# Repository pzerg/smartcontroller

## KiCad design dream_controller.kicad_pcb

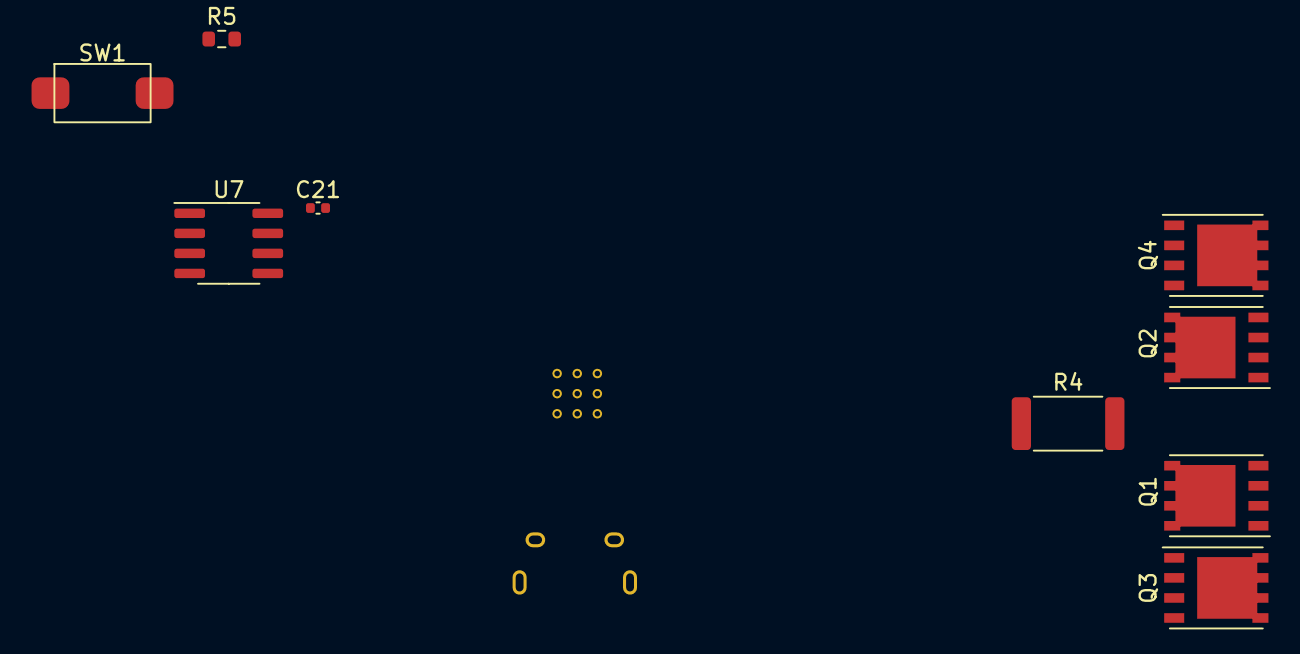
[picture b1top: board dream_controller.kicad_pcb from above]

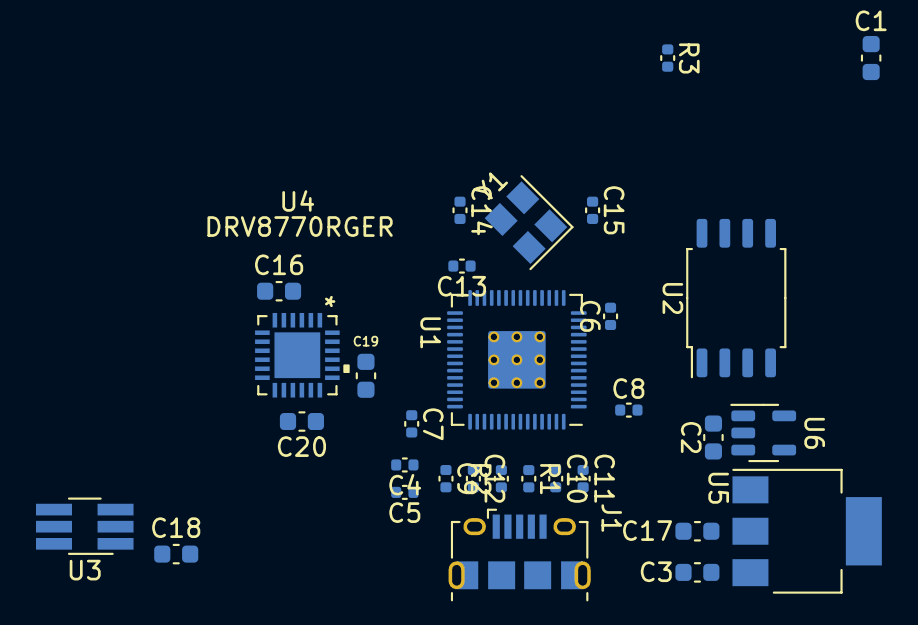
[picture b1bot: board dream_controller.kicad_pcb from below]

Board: 2 copper layers, 40 parts (31 on the bottom side), 30 nets, no tracks yet.

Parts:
C1: 100u; C_0603_1608Metric
C2, C3, C17: 10u; C_0603_1608Metric
C4, C5, C6, C7, C8, C9, C11, C12, C21: 100n; C_0402_1005Metric
C10, C13: 1u; C_0402_1005Metric
C14, C15: 14p; C_0402_1005Metric
C16: 10uF; C_0603_1608Metric
C18: 0.1u; C_0603_1608Metric
C19, C20: 100n; C_0603_1608Metric
J1: USB_B_Micro; USB_Micro-B_Amphenol_10118194_Horizontal
Q1, Q2, Q3, Q4: Q_NMOS_DGS; PowerPAK_SO-8_FET
R1, R2: 27; C_0402_1005Metric
R3: 1k; C_0402_1005Metric
R4: 0.3m; R_2512_6332Metric
R5: 1k; R_0603_1608Metric
SW1: SW_Push; PTS636
U1: RP2040; RP2040-QFN-56
U2: W25Q32JVSS; SOIC-8_5.23x5.23mm_P1.27mm
U3: MAX4073TAUT; TSOT-23-6_HandSoldering
U4: DRV8770RGER
U5: LM1117-3.3; SOT-223
U6: MAX40200AUK; SOT-23-5
U7: MAX3051; SOIC-8_3.9x4.9mm_P1.27mm
Y1: Crystal; Crystal_SMD_3225-4Pin_3.2x2.5mm

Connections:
+1V1: C11.1, C12.1, C13.1, U1.23 (DVDD), U1.45 (VREG_VOUT), U1.50 (DVDD)
+3V3: C1.1, C4.1, C5.1, C6.1, C7.1, C8.1, C9.1, C10.1, C17.1, C18.2, C21.2, R3.1, U1.1 (IOVDD), U1.10 (IOVDD), U1.22 (IOVDD), U1.33 (IOVDD), U1.42 (IOVDD), U1.43 (ADC_AVDD), U1.44 (VREG_IN), U1.48 (USB_VDD), U1.49 (IOVDD), U2.8 (VCC), U3.3 (VCC), U5.2 (VO), U7.3 (VDD)
+15V: C3.1, C16.2, U4.4 (GVDD), U5.3 (VI), U6.5 (OUT)
/CAN_RX: U1.18 (GPIO15), U7.4 (RXD)
/CAN_TX: U1.27 (GPIO16), U7.1 (TXD)
/Driver/GHA: Q1.2 (G), U4.19 (GHA)
/Driver/GHB: Q2.2 (G), U4.16 (GHB)
/Driver/GLA: Q3.2 (G), U4.11 (GLA)
/Driver/GLB: Q4.2 (G), U4.10 (GLB)
/Driver/M_A: Q1.3 (S), Q3.1 (D)
/Driver/M_B: Q2.3 (S), Q4.1 (D)
/Driver/RS-: Q1.1 (D), Q2.1 (D), R4.2, U3.5 (RS-)
/F_CLK: U1.52 (QSPI_SCLK), U2.6 (CLK)
/F_D0: U1.53 (QSPI_SD0), U2.5 (DI(IO0))
/F_D1: U1.55 (QSPI_SD1), U2.2 (DO(IO1))
/F_D2: U1.54 (QSPI_SD2), U2.3 (IO2)
/F_D3: U1.51 (QSPI_SD3), U2.7 (IO3)
/SS: R3.2, R5.2, U1.56 (QSPI_SS), U2.1 (~CS)
/USB_D+: J1.3 (D+), R1.2
/USB_D-: J1.2 (D-), R2.1
/VBUS: C2.1, J1.1 (VBUS), U6.1 (VDD), U6.3 (EN)
/XIN: C14.2, U1.20 (XIN), Y1.1
/XOUT: C15.2, U1.21 (XOUT), Y1.2
GND: C1.2, C2.2, C3.2, C4.2, C5.2, C6.2, C7.2, C8.2, C9.2, C10.2, C11.2, C12.2, C13.2, C14.1, C15.1, C16.1, C17.2, C18.1, C21.1, J1.5 (GND), J1.6 (Shield), Q3.3 (S), Q4.3 (S), SW1.1, U1.19 (TESTEN), U1.57 (GND), U2.4 (GND), U3.1 (GND), U3.2 (GND), U4.6 (GND), U4.12 (RSVD4), U4.25 (EPAD), U5.1 (GND), U6.2 (GND), U7.2 (GND), U7.5 (SHDN), U7.8 (RS)
unnamed: C19.1, U4.20 (BSTA)
unnamed: C20.1, U4.17 (BSTB)
unnamed: R1.1, U1.47 (USB_DP)
unnamed: R2.2, U1.46 (USB_DM)
unnamed: R5.1, SW1.2
VCC: C19.2, C20.2, R4.1, U3.4 (RS+), U4.15 (SHB), U4.18 (SHA)

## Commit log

2022-03-01 start
2022-03-13 added power
2022-04-14 added power for RP2040
2022-05-19 added SPI slave and master code
2022-05-19 finished schematic design
2022-05-19 assigned footprints and started PCB
2022-09-06 updating to CAN
2022-09-18 continued CANification
